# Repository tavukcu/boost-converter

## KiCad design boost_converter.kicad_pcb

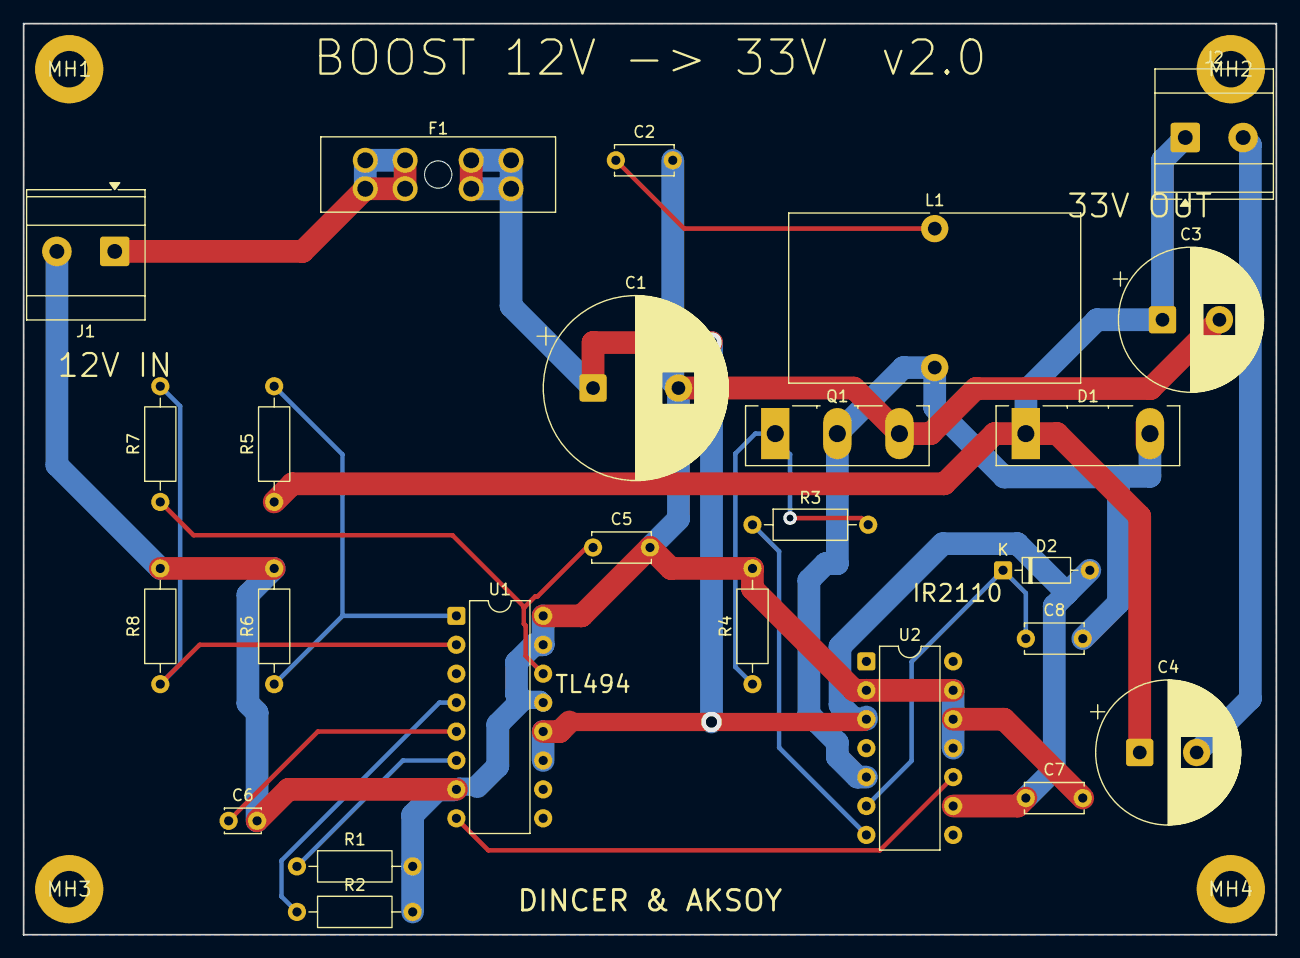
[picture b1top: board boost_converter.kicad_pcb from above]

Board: 2 copper layers, 110.0 x 80.0 mm, 29 parts (0 on the bottom side), 17 nets.

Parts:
C1: 2200uF; CP_Radial_D16.0mm_P7.50mm
C2, C5, C7: 100nF; C_Disc_D5.0mm_W2.5mm_P5.00mm
C3, C4: 470uF; CP_Radial_D12.5mm_P5.00mm
C6: 1nF; C_Disc_D3.0mm_W2.0mm_P2.50mm
C8: 1uF; C_Disc_D5.0mm_W2.5mm_P5.00mm
D1: MBR40250G; TO-247-2_Vertical
D2: 1N4148; D_DO-35_SOD27_P7.62mm_Horizontal
F1: 30A; FuseHolder_Blade_ATO_Littelfuse_FLR_178.6165
J1: 12V_IN; TerminalBlock_Phoenix_MKDS-3-2-5.08_1x02_P5.08mm_Horizontal
J2: 33V_OUT; TerminalBlock_Phoenix_MKDS-3-2-5.08_1x02_P5.08mm_Horizontal
L1: 22uH; L_Toroid_Vertical_L25.4mm_W14.7mm_P12.20mm_Vishay_TJ5
MH1, MH2, MH3, MH4: (no value)
Q1: IRFP4110; TO-247-3_Vertical
R1, R4, R7, R8: 10k; R_Axial_DIN0207_L6.3mm_D2.5mm_P10.16mm_Horizontal
R2: 47k; R_Axial_DIN0207_L6.3mm_D2.5mm_P10.16mm_Horizontal
R3: 10R; R_Axial_DIN0207_L6.3mm_D2.5mm_P10.16mm_Horizontal
R5: 100k; R_Axial_DIN0207_L6.3mm_D2.5mm_P10.16mm_Horizontal
R6: 5.6k; R_Axial_DIN0207_L6.3mm_D2.5mm_P10.16mm_Horizontal
U1: TL494; DIP-16_W7.62mm
U2: IR2110; DIP-14_W7.62mm

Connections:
+12V: C1.1, C7.1, D2.2, F1.2, U1.11, U1.12, U2.3, U2.9
/GATE: Q1.1, R3.2, R4.1
/PWM: U1.8, U2.10
/SW: C8.2, D1.2, L1.2, Q1.2, U2.5
/VOUT: C3.1, C4.1, D1.1, J2.1, R5.1
/VREF: C5.1, R7.1, U1.14
GND: C1.2, C2.2, C3.2, C5.2, C6.2, C7.2, J1.2, Q1.3, R1.2, R2.2, R4.2, R6.2, R8.2, U1.7, U1.13, U1.15, U1.16, U2.2, U2.11, U2.12, U2.13
unnamed: C2.1, L1.1
unnamed: C8.1, D2.1, U2.6
unnamed: F1.1, J1.1
unnamed: C4.2, J2.2
unnamed: R5.2, R6.1, U1.1
unnamed: R7.2, R8.1, U1.2
unnamed: C6.1, U1.5
unnamed: R2.1, U1.4
unnamed: R1.1, U1.6
unnamed: R3.1, U2.7
